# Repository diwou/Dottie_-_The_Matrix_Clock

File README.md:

# Dottie – The Matrix Clock

Eine Dot-Matrix-Uhr auf Basis einer **ESP32-S3-WROOM-1-N16R8-Platine** mit 16 MAX7219-LED-Matrix-Modulen, DS3231-RTC mit CR2032-Pufferung und VEML7700-Lichtsensor. Die Uhr zeigt Zeit und Datum mit Scroll-Animation, regelt die Helligkeit automatisch nach Umgebungslicht, synchronisiert die hochgenaue RTC per NTP und bietet eine Weboberfläche für Konfiguration, Diagnose, manuelle RTC-Einstellung und Firmware-Upload.

<p>
  
</p>

- Aktuelle Version: `1.5.0` (Development-Builds zeigen zusätzlich den Codeberg-Kurz-Hash)
- Repository: `https://codeberg.org/diwou/Dottie_-_The_Matrix_Clock`
- Browser-Installer: [https://diwou.codeberg.page/Dottie_-_The_Matrix_Clock/](https://diwou.codeberg.page/Dottie_-_The_Matrix_Clock/)
- Web-UI im Gerät: [http://dottie.local/](http://dottie.local/) im lokalen Netz
- Lizenz: `CC BY-NC-SA 4.0`

---

## Features

- **Zeitbasis**: DS3231-RTC als Laufzeit-Uhr, NTP zur regelmäßigen Korrektur und manuelle RTC-Einstellung im Webinterface
- **NTP-Synchronisation** mit 3 konfigurierbaren Fallback-Servern
- **Zeitzone & DST**: UTC-Offset, EU/US/Custom-Sommerzeit
- **Display**: 24h/12h-Modus, 5 Datumsformate, einstellbare Helligkeit, Scroll-Animation, Software-Dimmen und VEML7700-Autohelligkeit
- **Web-UI**: Responsive HTML5-Oberfläche mit Live-Display-Vorschau, RTC-Tab, NTP-Status, Diagnose, Firmware-Installer und umschaltbarem Light-/Dark-Mode
- **OTA-/Firmware-Updates**: Kabellose Updates über `dottie.local` und Web-Upload von `.bin`-Firmwaredateien
- **WiFi-Resilienz**: State-Machine mit exponentiellem Backoff, AP-Fallback (Captive Portal)
- **Factory-Reset**: konfigurierbarer GPIO 5 Sekunden halten

---

## Hardware

| Komponente | Details |
|---|---|
| MCU | ESP32-S3-WROOM-1-N16R8 |
| Display | 16× MAX7219 LED-Matrix-Module (FC16_HW) |
| Display-Pins | DIN = GPIO11, CLK = GPIO12, CS/LOAD = GPIO10 |
| I2C | SDA = GPIO38, SCL = GPIO39 für VEML7700 und DS3231S |
| RTC | DS3231S als Laufzeit-Uhr, CR2032-batteriegepuffert, NTP schreibt Korrekturen zurück in die RTC |
| Anordnung | 2 Reihen: TOP (8 Module, 8×8 px) + BOTTOM (8 Module, 5×7 px) |
| Reset-Button | GPIO9 gegen GND, 5 Sekunden halten |

## KiCad

Der KiCad-Projektspiegel liegt unter [kicad/README.md](kicad/README.md).

| Pfad | Inhalt |
|---|---|
| `kicad/source/` | KiCad-Quellen des Boards |
| `kicad/fab/rev0.4/` | Fertigungsdaten für die aktuelle Hardwarefreigabe `0.4` |

Die vollständige Stückliste liegt in `kicad/fab/rev0.4/bom.csv`, die zugehörigen Bestückungsdaten in `positions.csv` und die Freigabe als Paket in `Dottie_-_The_Matrix_Clock_0.4.zip`.

### Verdrahtung

```
ESP32-S3 → MAX7219-Kette
GPIO11 → DIN
GPIO12 → CLK
GPIO10 → CS/LOAD
```

Die Pinwerte werden in `platformio.ini` über `DISPLAY_DATA_PIN`, `DISPLAY_CLK_PIN`, `DISPLAY_CS_PIN`, `FACTORY_RESET_PIN`, `I2C_SDA_PIN` und `I2C_SCL_PIN` gesetzt.

Die 16 Module bilden eine SPI-Kette: TOP (Module 0–7, rechts nach links) und BOTTOM (Module 8–15, rechts nach links). Das physikalische Mapping wird über `MAP_TOP[]` und `MAP_BOTTOM[]` in `display.h` konfiguriert.

---

## Software / Build

**Werkzeug:** PlatformIO (VSCode/VSCodium Extension oder CLI)

```bash
# Kompilieren
pio run -e dottie_esp32s3

# OTA-Upload (IP per CLI angeben)
pio run -t upload -e dottie_esp32s3_ota --upload-port dottie.local

# Wenn das Board nur im AP-Modus laeuft:
# pio run -t upload -e dottie_esp32s3_ota --upload-port 192.168.4.1

# VS Codium: Task "PIO OTA Upload (ESP32-S3)"
# (nutzt das OTA-Env direkt und umgeht den fehlerhaften Upload-Dialog)

# Native USB am ESP32-S3
pio run -t upload -e dottie_esp32s3 --upload-port /dev/serial/by-id/usb-Espressif_USB_JTAG_serial_debug_unit_94-A9-90-2F-91-A0-if00

# Firmware-Build-Artefakte
# `Firmware/<version>/` und `Firmware/latest/` werden beim Build automatisch erzeugt

# Firmware-Installer im Webinterface
# Im Web-UI unter `System` -> `Firmware-Installer` die `.bin` aus `Firmware/latest/` hochladen.

# Serieller Monitor (USB-Fallback, 115200 Baud)
pio device monitor
```

### Abhängigkeiten

| Bibliothek | Version |
|---|---|
| `majicdesigns/MD_MAX72XX` | ^3.5.1 |
| `adafruit/Adafruit VEML7700 Library` | ^2.1.6 |
| ESP32 Arduino Core (PlatformIO `espressif32`) | – |

---

## Inbetriebnahme

1. Firmware per USB oder OTA flashen; bei OTA die Geräte-IP über `--upload-port` angeben
2. Firmware flashen: `pio run -t upload -e dottie_esp32s3`
3. Beim ersten Start ohne gespeicherte WLAN-Konfiguration öffnet Dottie einen **AP** mit SSID `DOTTIE-{ChipID}`
4. Mit dem AP verbinden (IP: `192.168.4.1`) und WLAN-Zugangsdaten eingeben
5. Nach dem Verbinden ist die Web-UI unter der zugewiesenen IP oder `http://dottie.local` erreichbar

---

## Web-Oberfläche

### Tabs

| Tab | Inhalt |
|---|---|
| **Status** | WiFi-Status, IP, NTP-Log (letzte 5 Syncs), manueller NTP-Test |
| **WiFi** | SSID, Passwort, Timeout, DHCP/Static-IP, DNS |
| **NTP** | 3 Server-URLs, Sync-Intervall, Test-Buttons |
| **RTC** | DS3231-Status, I2C-Diagnose, letzter NTP-Sync, manuelle Uhrzeit/Datum-Eingabe |
| **Zeitzone** | UTC-Offset, DST-Modus (Aus/EU/US/Custom) |
| **Display** | 24h/12h, Sekunden, Datumsformat, Helligkeit, Scroll-Effekt, VEML7700-Autohelligkeit |
| **System** | OTA, Firmware-Installer, Dark-Mode, Chip-Info, Neustart, Factory-Reset, Diagnose |

### REST-API

| Endpoint | Methode | Beschreibung |
|---|---|---|
| `/api/status` | GET | JSON: Zeit, Datum, Uptime, next_sync, Heap, RSSI |
| `/api/ntptest` | GET | JSON: running, host, result, detail |
| `/api/update` | POST | Firmware per Web-Upload einspielen |
| `/rtcset` | POST | RTC manuell auf Datum und Uhrzeit setzen |
| `/save` | POST | Konfiguration speichern |
| `/test?i=1..3` | POST | NTP-Server testen (asynchron) |
| `/reboot` | POST | Neustart |
| `/factory` | POST | Factory-Reset |
| `/diag` | GET | Diagnose-Seite (Debug-Info) |

---

## Konfiguration

Die Konfiguration wird als `Key=Value`-Datei auf LittleFS unter `/cfg.txt` gespeichert. Kommentare mit `#` sind erlaubt.

### Wichtige Parameter

| Schlüssel | Standardwert | Beschreibung |
|---|---|---|
| `ntp1..3` | pool.ntp.org, time.google.com, time.cloudflare.com | NTP-Server |
| `ntp_interval_min` | 15 | Sync-Intervall in Minuten (0 = 15) |
| `utc_offset_min` | 60 | UTC-Offset in Minuten (UTC+1 = 60) |
| `dst_mode` | 1 | 0=Aus, 1=EU, 2=US, 3=Custom |
| `date_fmt` | 0 | Datumsformat (0–4, s.u.) |
| `show_24h` | 1 | 24h-Modus (0 = 12h mit AM/PM) |
| `show_seconds` | 1 | Sekunden anzeigen (nur 24h) |
| `brightness` | 1 | Display-Helligkeit (0–15) |
| `auto_brightness` | 0 | Helligkeit automatisch per VEML7700 regeln |
| `scroll_enabled` | 1 | Scroll-Animation beim Ziffernwechsel |
| `pwm_duty` | 10 | Software-Dimmen (10 = aus, 1–5 = 10–50 % Abdunklung) |

### Datumsformate

| Wert | Format | Beispiel |
|---|---|---|
| 0 | `DD.MM.YYYY` | 07.03.2026 |
| 1 | `MM/DD/YYYY` | 03/07/2026 |
| 2 | `YYYY-MM-DD` | 2026-03-07 |
| 3 | `DD.MM.YY` | 07.03.26 |
| 4 | `MM/DD/YY` | 03/07/26 |

---

## Architektur

### Dateistruktur

| Datei | Rolle |
|---|---|
| `src/main.cpp` | Kernlogik: Boot, WiFi-State-Machine, NTP-Sync, OTA, Loop |
| `src/config.h` | Config-Struct, LittleFS-Load/Save (`/cfg.txt`), Makro-Parser, `APP_VERSION_BASE` |
| `src/display.h` | Bitmap-Glyphen (8×8 + 5×7), Scroll-Animation, Display-Mapping |
| `src/ClockWebUi.h` | HTML5-WebUI (Tabs), REST-APIs, JavaScript-Glyphen-Renderer |
| `platformio.ini` | Build-Konfiguration, Bibliotheksabhängigkeiten |

### WiFi-State-Machine

```
CONNECTED
  ↓ (Verbindungsverlust)
DISCONNECTED
  ↓ (nach Backoff: 30s → 60s → 120s → 300s max)
RECONNECTING
  ↓ (max. Fehlversuche erreicht)
AP_MODE (Captive Portal: SSID DOTTIE-{ChipID}, IP 192.168.4.1)
```

### NTP-Synchronisation

1. DNS-Auflösung (3 Versuche, lwIP-Direktfallback)
2. IP-Cache (3 Einträge) für schnelle Re-Syncs
3. UDP-Probe nach RFC 5905, Timeout 900 ms
4. 3 Server werden getestet, erster erfolgreicher wird verwendet
5. Log-Ringpuffer (5 Einträge) in der Web-UI sichtbar

### Display-Mapping

Physikalische Modul-IDs werden über `MAP_TOP[8]` und `MAP_BOTTOM[8]` von logischen Positionen entkoppelt. Flip/Mirror/Rotate für das Bottom-Display sind über Defines konfigurierbar (`BOTTOM_FLIP_VERTICAL_8`).

### OTA

- Hostname: `dottie.local` (mDNS)
- Progress-Anzeige auf dem Matrix-Display (Prozentbalken)
- OTA-Passwort optional konfigurierbar

---

## Factory-Reset

Den in `FACTORY_RESET_PIN` konfigurierten GPIO für **5 Sekunden** gegen GND halten:
- Countdown wird auf dem Display angezeigt
- `/cfg.txt` wird gelöscht
- Gerät startet neu und öffnet AP

---

## Lizenz

Dieses Projekt steht unter der Lizenz `Creative Commons Attribution-NonCommercial-ShareAlike 4.0 International (CC BY-NC-SA 4.0)`.

Lizenztext: `LICENSE`

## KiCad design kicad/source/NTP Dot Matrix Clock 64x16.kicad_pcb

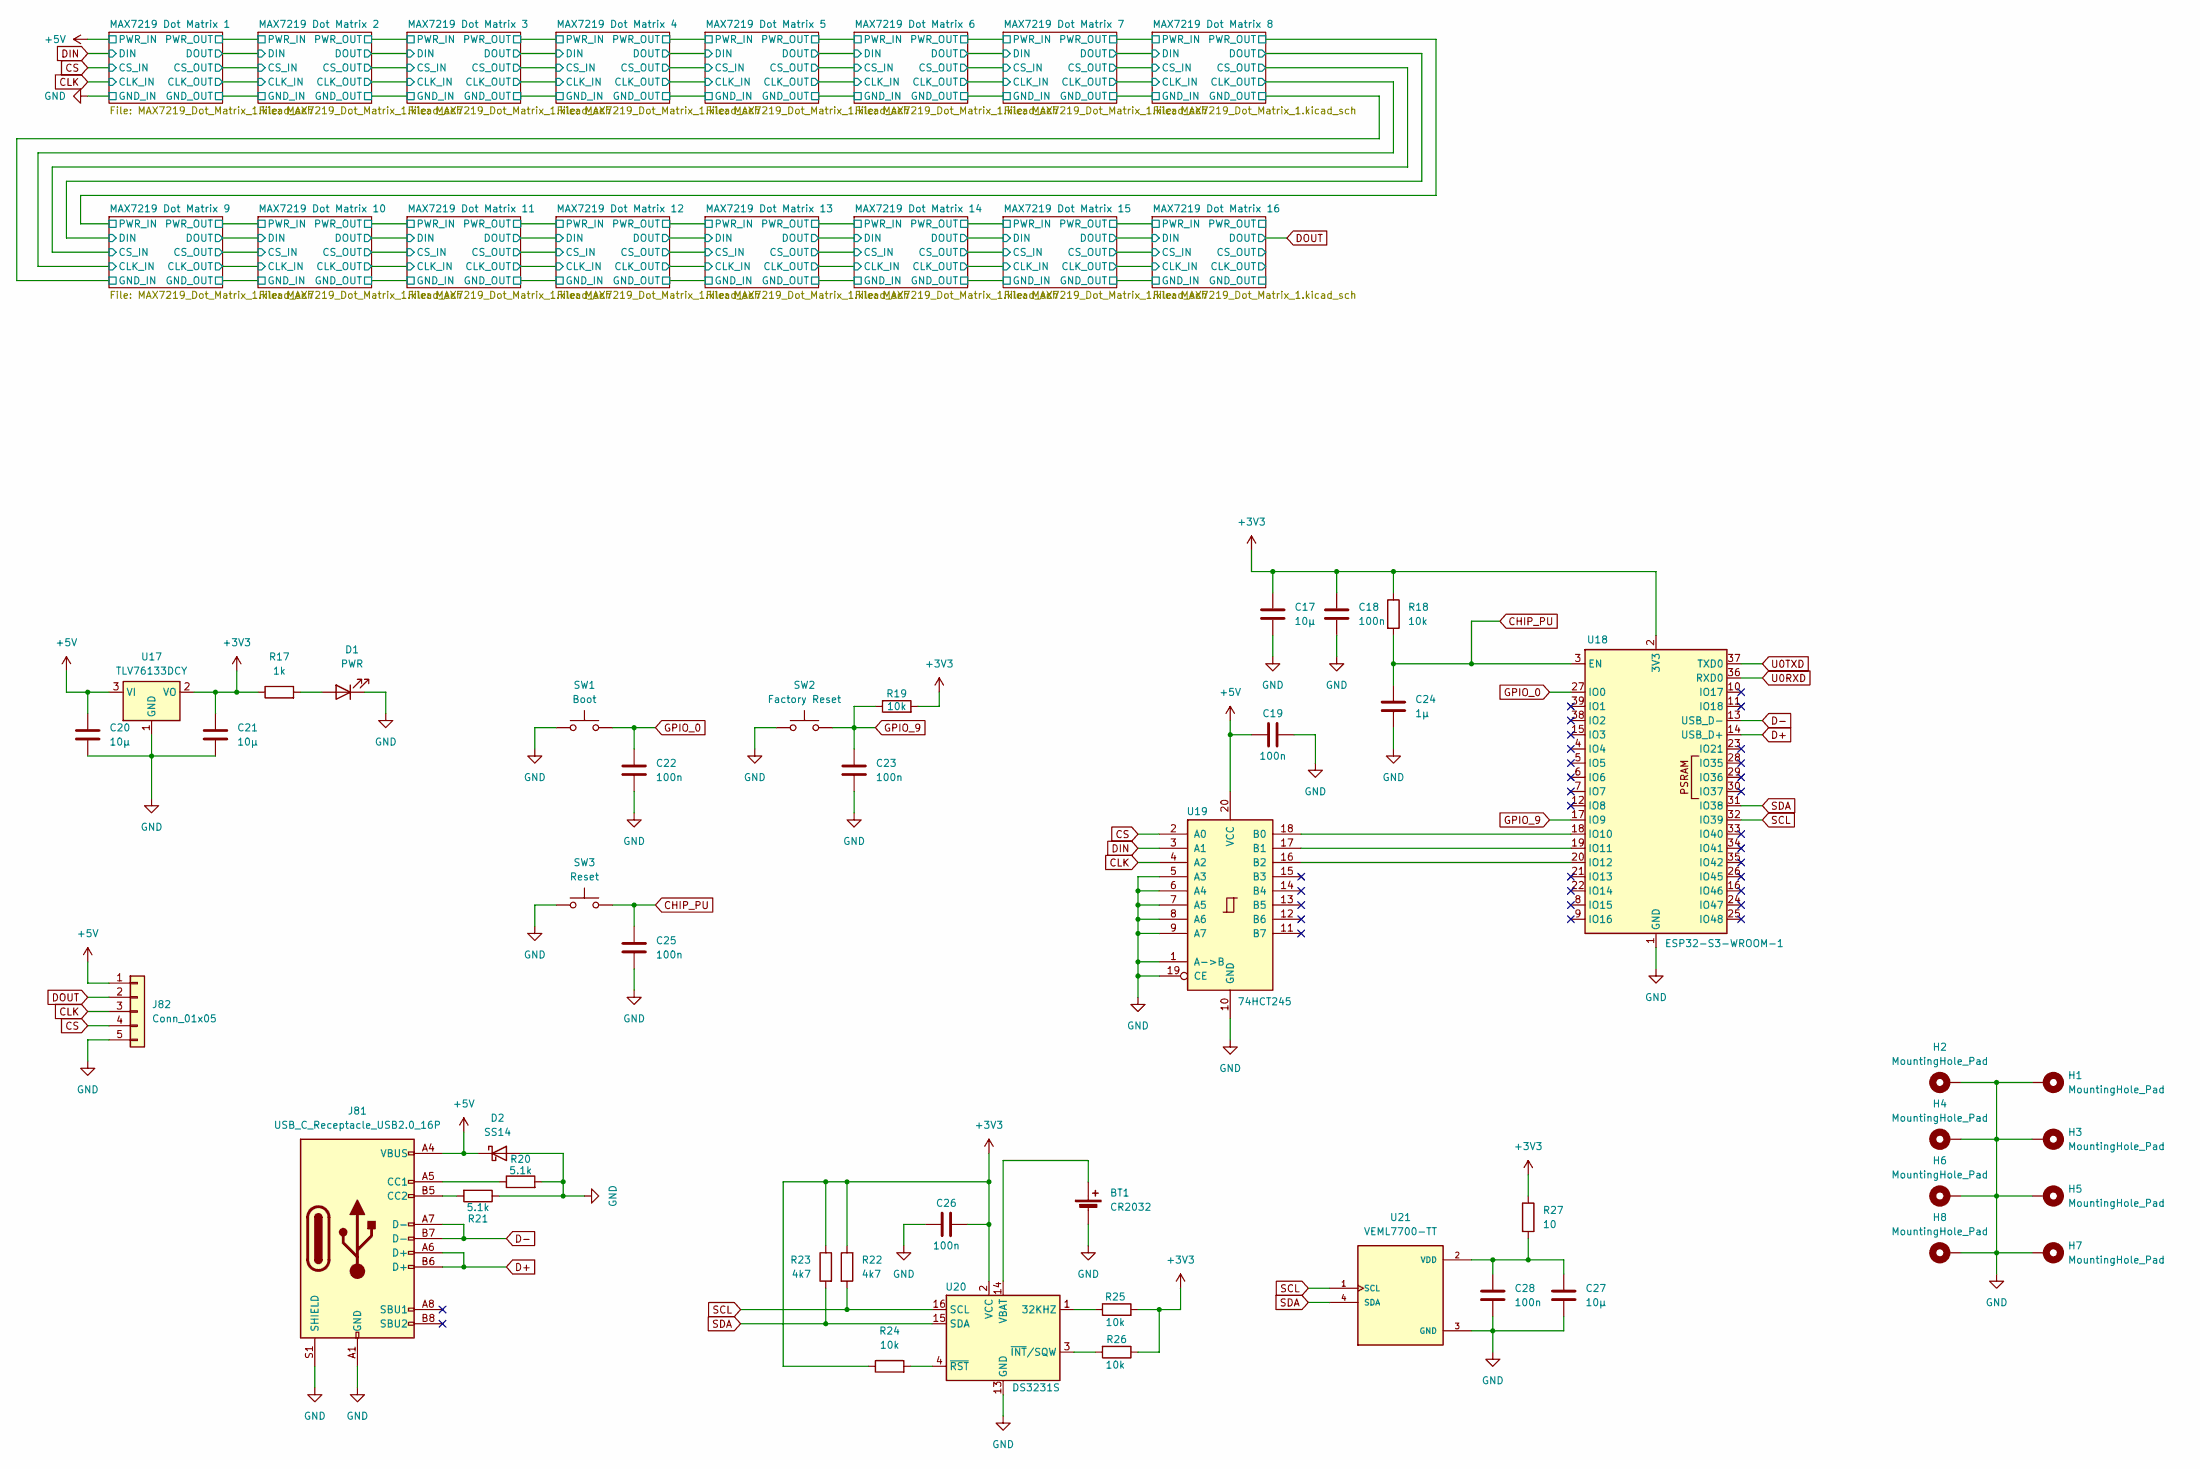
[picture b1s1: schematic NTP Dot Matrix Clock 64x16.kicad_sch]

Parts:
BT1: CR2032; BatteryHolder_MYOUNG_BS-07-A1BJ001_CR2032
C17, C27: 10µ; C_0805_2012Metric_Pad1.18x1.45mm_HandSolder
C18, C19, C22, C23, C25, C26, C28: 100n; C_0805_2012Metric_Pad1.18x1.45mm_HandSolder
C20, C21: 10µ; C_1206_3216Metric_Pad1.33x1.80mm_HandSolder
C24: 1µ; C_0805_2012Metric_Pad1.18x1.45mm_HandSolder
D1: PWR; LED_0805_2012Metric_Pad1.15x1.40mm_HandSolder
D2: SS14; D_SMA
H1, H2, H3, H4, H5, H6, H7, H8: MountingHole_Pad; MountingHole_3.2mm_M3_DIN965_Pad
J81: USB_C_Receptacle_USB2.0_16P; USB_C_Receptacle_HCTL_HC-TYPE-C-16P-01A
J82: Conn_01x05; PinHeader_1x05_P2.54mm_Vertical
R17: 1k; R_0805_2012Metric_Pad1.20x1.40mm_HandSolder
R18, R19, R24, R25, R26: 10k; R_0805_2012Metric_Pad1.20x1.40mm_HandSolder
R20, R21: 5.1k; R_0805_2012Metric_Pad1.20x1.40mm_HandSolder
R22, R23: 4k7; R_0805_2012Metric_Pad1.20x1.40mm_HandSolder
R27: 10; R_0805_2012Metric_Pad1.20x1.40mm_HandSolder
SW1: Boot; SW_PUSH_6mm_H5mm
SW2: Factory Reset; SW_PUSH_6mm_H5mm
SW3: Reset; SW_PUSH_6mm_H5mm
U17: TLV76133DCY; SOT-223-3_TabPin2
U18: ESP32-S3-WROOM-1
U19: 74HCT245; TSSOP-20_4.4x6.5mm_P0.65mm
U20: DS3231S; SOIC-16W_7.5x10.3mm_P1.27mm
U21: VEML7700-TT; XDCR_VEML7700-TT; PARTREV 1.6

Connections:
+3V3: C17.1, C18.1, C21.1, C26.2, R17.1, R18.1, R19.2, R22.1, R23.1, R24.1, R25.2, R26.1, R27.1, U17.2 (VO), U18.2 (3V3), U20.2 (VCC)
+5V: C19.1, C20.1, D2.1 (K), J81.A4 (VBUS), J81.A9 (VBUS), J81.B4 (VBUS), J81.B9 (VBUS), J82.1, U17.3 (VI), U19.20 (VCC); also elsewhere on the board
CHIP_PU: C24.1, C25.1, R18.2, SW3.2, U18.3 (EN)
CLK: J82.3, U19.4 (A2); also elsewhere on the board
CS: J82.4, U19.2 (A0); also elsewhere on the board
D+: J81.A6 (D+), J81.B6 (D+), U18.14 (USB_D+)
D-: J81.A7 (D-), J81.B7 (D-), U18.13 (USB_D-)
DIN: U19.3 (A1); also elsewhere on the board
DOUT: J82.2; also elsewhere on the board
GND: BT1.2 (-), C17.2, C18.2, C19.2, C20.2, C21.2, C22.2, C23.2, C24.2, C25.2, C26.1, C27.2, C28.2, D1.1 (K), D2.2 (A), H1.1 (1_1), H2.1 (1_1), H3.1 (1_1), H4.1 (1_1), H5.1 (1_1), H6.1 (1_1), H7.1 (1_1), H8.1 (1_1), J81.A1 (GND), J81.A12 (GND), J81.B1 (GND), J81.B12 (GND), J81.S1 (SHIELD), J82.5, R20.2, R21.1, SW1.1, SW2.1, SW3.1, U17.1 (GND), U18.1 (GND), U18.40 (GND), U18.41 (GND), U19.1 (A->B), U19.5 (A3), U19.6 (A4), U19.7 (A5), U19.8 (A6), U19.9 (A7), U19.10 (GND), U19.19 (CE), U20.5 (GND), U20.6 (GND), U20.7 (GND), U20.8 (GND), U20.9 (GND), U20.10 (GND), U20.11 (GND), U20.12 (GND), U20.13 (GND), U21.3 (GND); also elsewhere on the board
GPIO_0: C22.1, SW1.2, U18.27 (IO0)
GPIO_9: C23.1, R19.1, SW2.2, U18.17 (IO9)
unnamed: BT1.1 (+), U20.14 (VBAT)
unnamed: D1.2 (A), R17.2
unnamed: J81.A5 (CC1), R20.1
unnamed: J81.B5 (CC2), R21.2
unnamed: U18.18 (IO10), U19.18 (B0)
unnamed: U18.19 (IO11), U19.17 (B1)
unnamed: U18.20 (IO12), U19.16 (B2)
unnamed: R25.1, U20.1 (32KHZ)
unnamed: R26.2, U20.3 (~INT/SQW)
unnamed: R24.2, U20.4 (~RST)
unnamed: C27.1, C28.1, R27.2, U21.2 (VDD)
SCL: R22.2, U18.32 (IO39), U20.16 (SCL), U21.1 (SCL)
SDA: R23.2, U18.31 (IO38), U20.15 (SDA), U21.4 (SDA)
U0RXD: U18.36 (RXD0)
U0TXD: U18.37 (TXD0)

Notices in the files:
kicad/source/NTP Dot Matrix Clock 64x16.kicad_pcb:
© 2026  Dirk Wouters
License: CC BY-NC-SA 4.0
